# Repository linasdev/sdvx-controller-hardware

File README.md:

# Sound Voltex Controller Hardware
This repository contains hardware for an open-sorce [Sound Voltex](https://en.wikipedia.org/wiki/Sound_Voltex) controller.

# License
This project is licensed under the MIT License - see the [LICENSE.md](LICENSE.md) file for details.

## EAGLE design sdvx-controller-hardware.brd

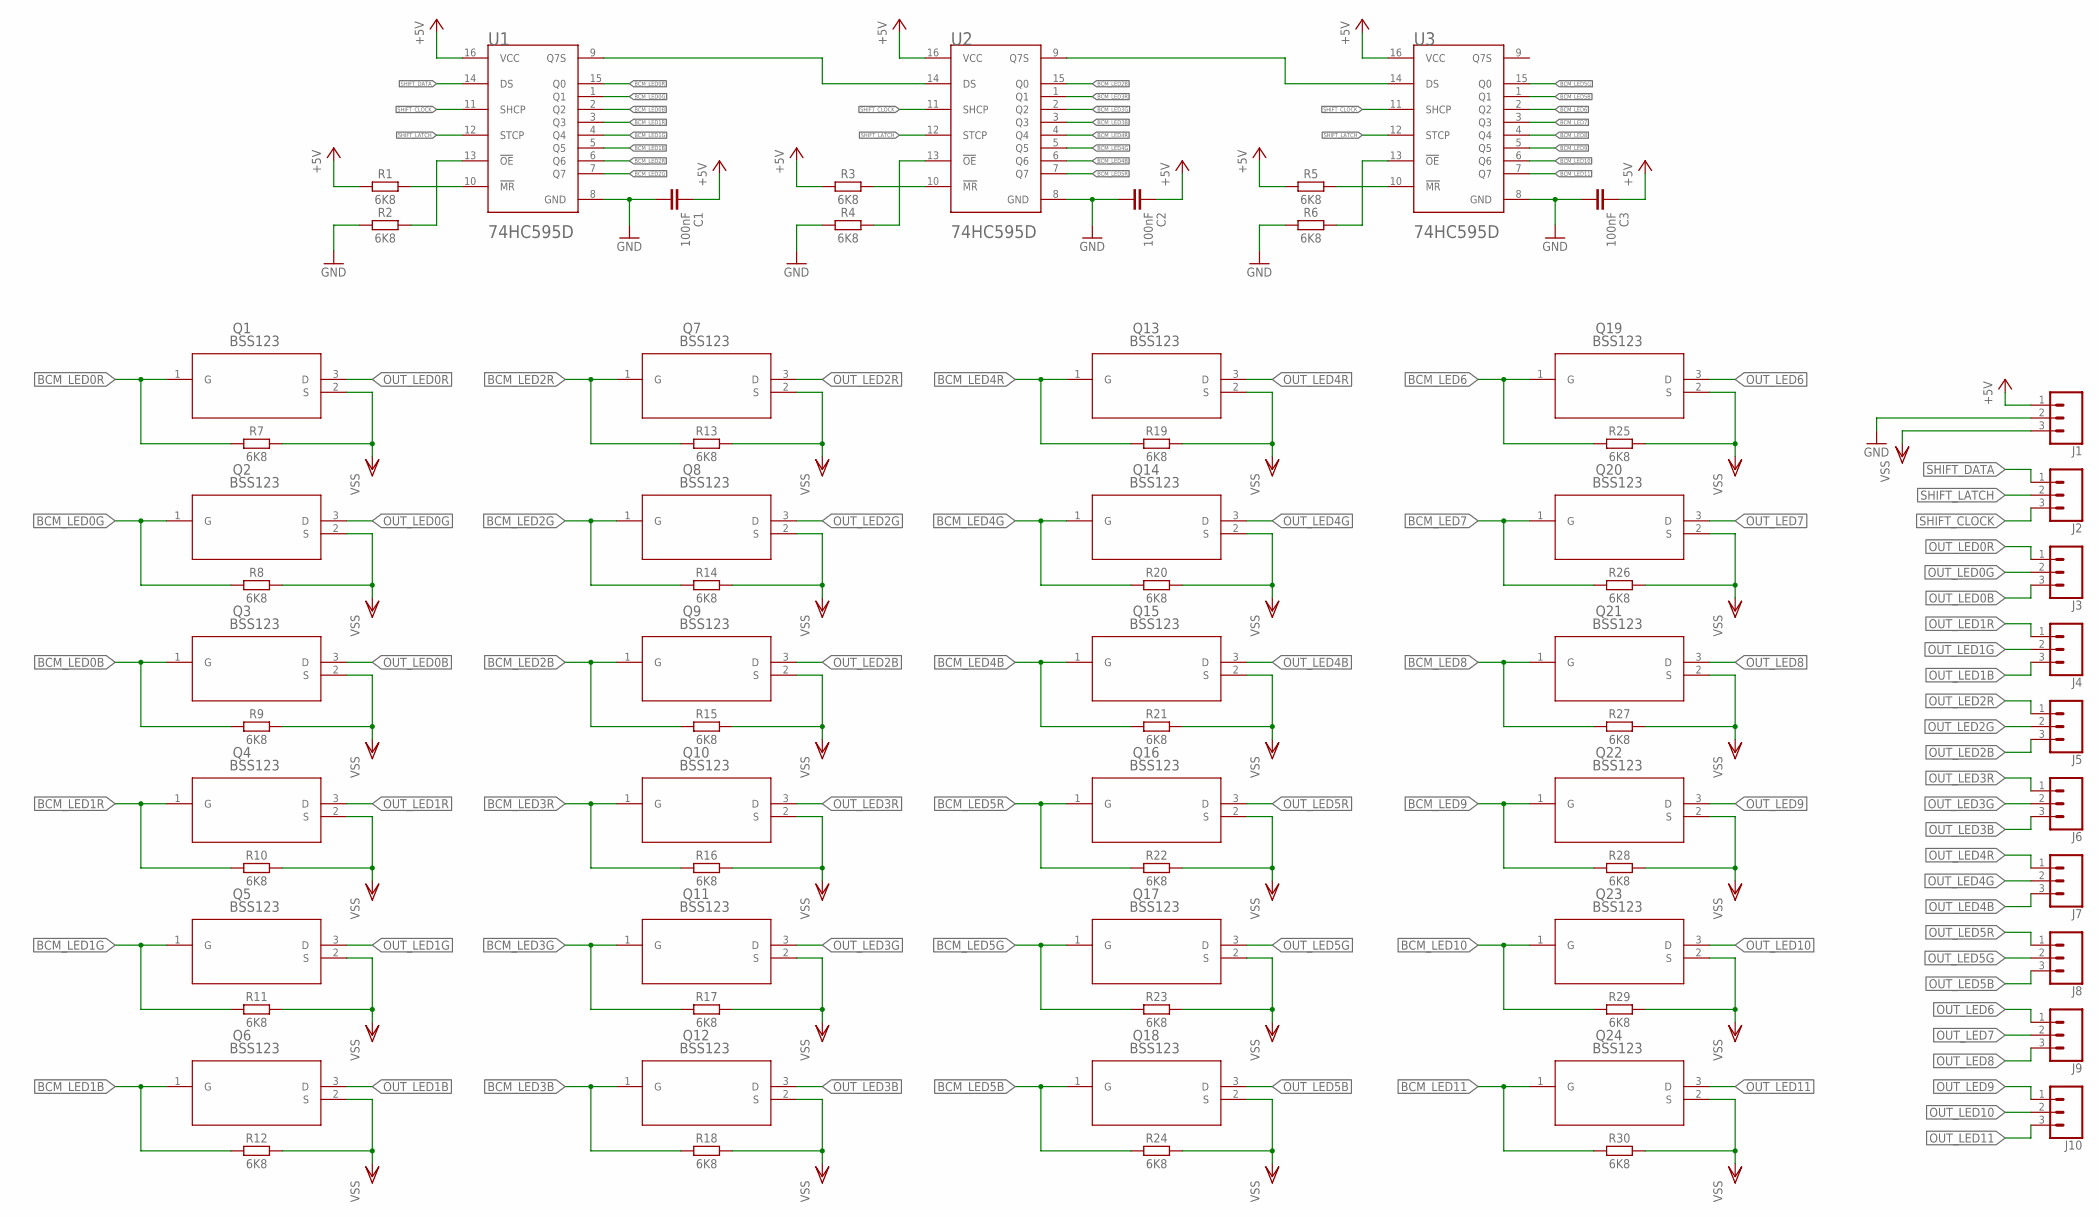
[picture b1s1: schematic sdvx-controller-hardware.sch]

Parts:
C1, C2, C3: 100nF; CAPC2012X110
J1, J2, J3, J4, J5, J6, J7, J8, J9, J10: CONN_03-SCREW-5MM; SCREWTERMINAL-5MM-3
Q1, Q2, Q3, Q4, Q5, Q6, Q7, Q8, Q9, Q10, Q11, Q12, Q13, Q14, Q15, Q16, Q17, Q18, Q19, Q20, Q21, Q22, Q23, Q24: BSS123; SOT-23-3_1P4X3P040_ONS
R1, R2, R3, R4, R5, R6, R7, R8, R9, R10, R11, R12, R13, R14, R15, R16, R17, R18, R19, R20, R21, R22, R23, R24, R25, R26, R27, R28, R29, R30: 6K8; RESC2012X65
U1, U2, U3: NEXPERIA_74HC595DNEXPERIA_74HC595D_0_0; NEXPERIA_74HC595D_0

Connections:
+5V: C1.1, C2.1, C3.1, J1.1, R1.1, R3.1, R5.1, U1.16 (VCC), U2.16 (VCC), U3.16 (VCC)
BCM_LED0B: Q3.1 (G), R9.1, U1.2 (Q2)
BCM_LED0G: Q2.1 (G), R8.1, U1.1 (Q1)
BCM_LED0R: Q1.1 (G), R7.1, U1.15 (Q0)
BCM_LED1B: Q6.1 (G), R12.1, U1.5 (Q5)
BCM_LED1G: Q5.1 (G), R11.1, U1.4 (Q4)
BCM_LED1R: Q4.1 (G), R10.1, U1.3 (Q3)
BCM_LED2B: Q9.1 (G), R15.1, U2.15 (Q0)
BCM_LED2G: Q8.1 (G), R14.1, U1.7 (Q7)
BCM_LED2R: Q7.1 (G), R13.1, U1.6 (Q6)
BCM_LED3B: Q12.1 (G), R18.1, U2.3 (Q3)
BCM_LED3G: Q11.1 (G), R17.1, U2.2 (Q2)
BCM_LED3R: Q10.1 (G), R16.1, U2.1 (Q1)
BCM_LED4B: Q15.1 (G), R21.1, U2.6 (Q6)
BCM_LED4G: Q14.1 (G), R20.1, U2.5 (Q5)
BCM_LED4R: Q13.1 (G), R19.1, U2.4 (Q4)
BCM_LED5B: Q18.1 (G), R24.1, U3.1 (Q1)
BCM_LED5G: Q17.1 (G), R23.1, U3.15 (Q0)
BCM_LED5R: Q16.1 (G), R22.1, U2.7 (Q7)
BCM_LED6: Q19.1 (G), R25.1, U3.2 (Q2)
BCM_LED7: Q20.1 (G), R26.1, U3.3 (Q3)
BCM_LED8: Q21.1 (G), R27.1, U3.4 (Q4)
BCM_LED9: Q22.1 (G), R28.1, U3.5 (Q5)
BCM_LED10: Q23.1 (G), R29.1, U3.6 (Q6)
BCM_LED11: Q24.1 (G), R30.1, U3.7 (Q7)
GND: C1.2, C2.2, C3.2, J1.2, R2.1, R4.1, R6.1, U1.8 (GND), U2.8 (GND), U3.8 (GND)
unnamed: R1.2, U1.10 (!MR!)
unnamed: R2.2, U1.13 (!OE!)
unnamed: R4.2, U2.13 (!OE!)
unnamed: R3.2, U2.10 (!MR!)
unnamed: R6.2, U3.13 (!OE!)
unnamed: R5.2, U3.10 (!MR!)
unnamed: U1.9 (Q7S), U2.14 (DS)
unnamed: U2.9 (Q7S), U3.14 (DS)
OUT_LED0B: J3.3, Q3.3 (D)
OUT_LED0G: J3.2, Q2.3 (D)
OUT_LED0R: J3.1, Q1.3 (D)
OUT_LED1B: J4.3, Q6.3 (D)
OUT_LED1G: J4.2, Q5.3 (D)
OUT_LED1R: J4.1, Q4.3 (D)
OUT_LED2B: J5.3, Q9.3 (D)
OUT_LED2G: J5.2, Q8.3 (D)
OUT_LED2R: J5.1, Q7.3 (D)
OUT_LED3B: J6.3, Q12.3 (D)
OUT_LED3G: J6.2, Q11.3 (D)
OUT_LED3R: J6.1, Q10.3 (D)
OUT_LED4B: J7.3, Q15.3 (D)
OUT_LED4G: J7.2, Q14.3 (D)
OUT_LED4R: J7.1, Q13.3 (D)
OUT_LED5B: J8.3, Q18.3 (D)
OUT_LED5G: J8.2, Q17.3 (D)
OUT_LED5R: J8.1, Q16.3 (D)
OUT_LED6: J9.1, Q19.3 (D)
OUT_LED7: J9.2, Q20.3 (D)
OUT_LED8: J9.3, Q21.3 (D)
OUT_LED9: J10.1, Q22.3 (D)
OUT_LED10: J10.2, Q23.3 (D)
OUT_LED11: J10.3, Q24.3 (D)
SHIFT_CLOCK: J2.3, U1.11 (SHCP), U2.11 (SHCP), U3.11 (SHCP)
SHIFT_DATA: J2.1, U1.14 (DS)
SHIFT_LATCH: J2.2, U1.12 (STCP), U2.12 (STCP), U3.12 (STCP)
VSS: J1.3, Q1.2 (S), Q2.2 (S), Q3.2 (S), Q4.2 (S), Q5.2 (S), Q6.2 (S), Q7.2 (S), Q8.2 (S), Q9.2 (S), Q10.2 (S), Q11.2 (S), Q12.2 (S), Q13.2 (S), Q14.2 (S), Q15.2 (S), Q16.2 (S), Q17.2 (S), Q18.2 (S), Q19.2 (S), Q20.2 (S), Q21.2 (S), Q22.2 (S), Q23.2 (S), Q24.2 (S), R7.2, R8.2, R9.2, R10.2, R11.2, R12.2, R13.2, R14.2, R15.2, R16.2, R17.2, R18.2, R19.2, R20.2, R21.2, R22.2, R23.2, R24.2, R25.2, R26.2, R27.2, R28.2, R29.2, R30.2

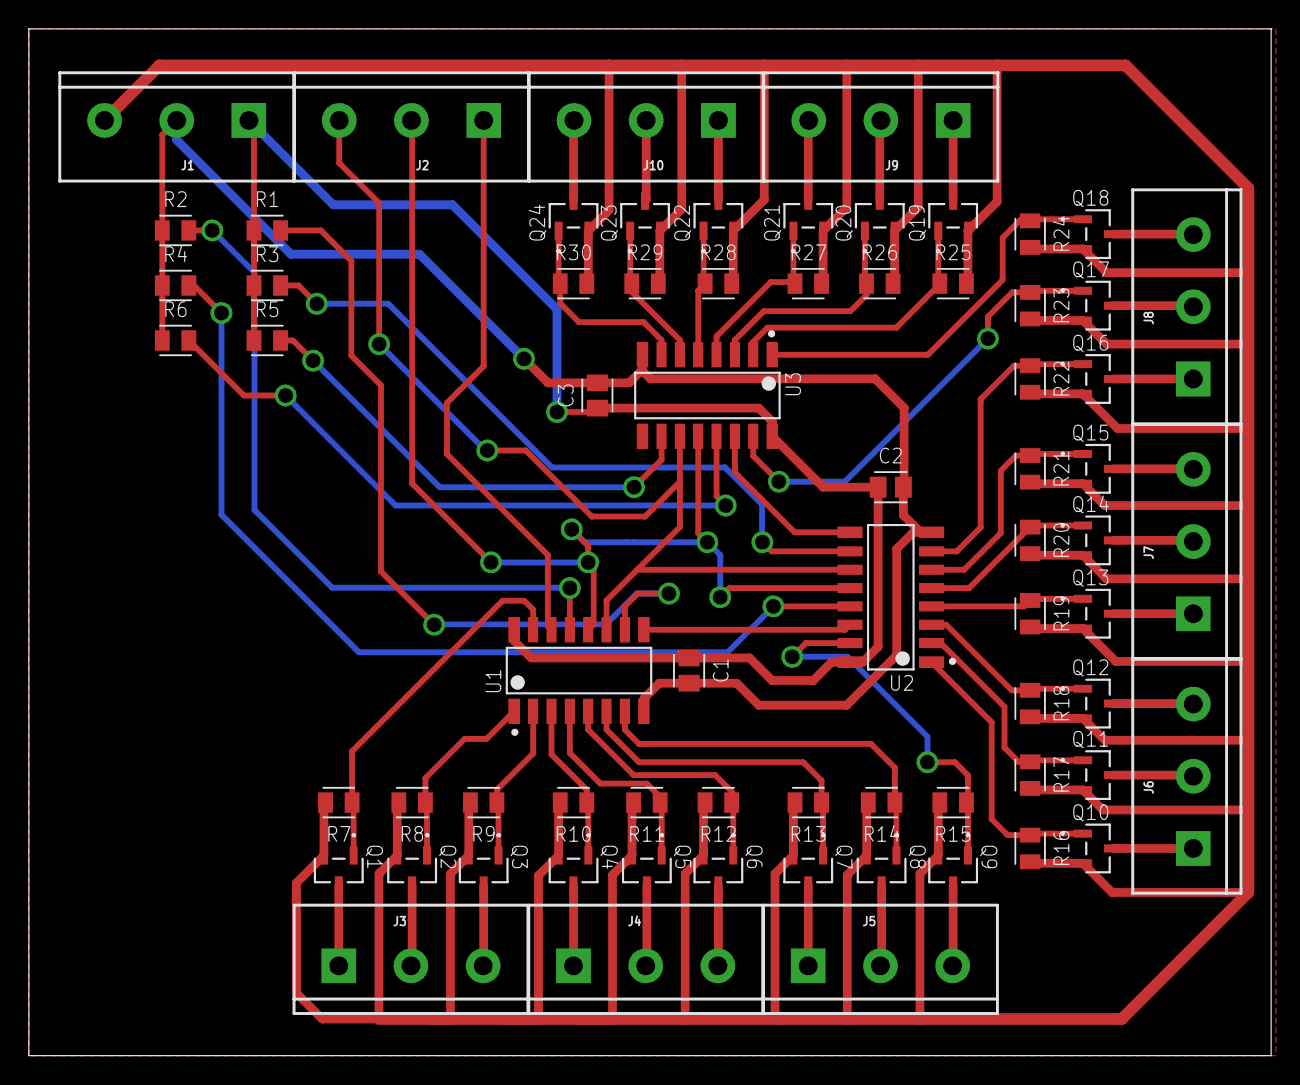
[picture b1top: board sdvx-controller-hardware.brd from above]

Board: 2 copper layers, 86.0 x 71.1 mm, 70 parts (0 on the bottom side), 62 nets.

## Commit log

2021-08-28 Create initial design

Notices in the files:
parts and their libraries:
SparkFun-Connectors: Licensing: Creative Commons ShareAlike 4.0 International - https://creativecommons.org/licenses/by-sa/4.0
COPYRIGHT: Copyright (C) 2021 Ultra Librarian. All rights reserved.
